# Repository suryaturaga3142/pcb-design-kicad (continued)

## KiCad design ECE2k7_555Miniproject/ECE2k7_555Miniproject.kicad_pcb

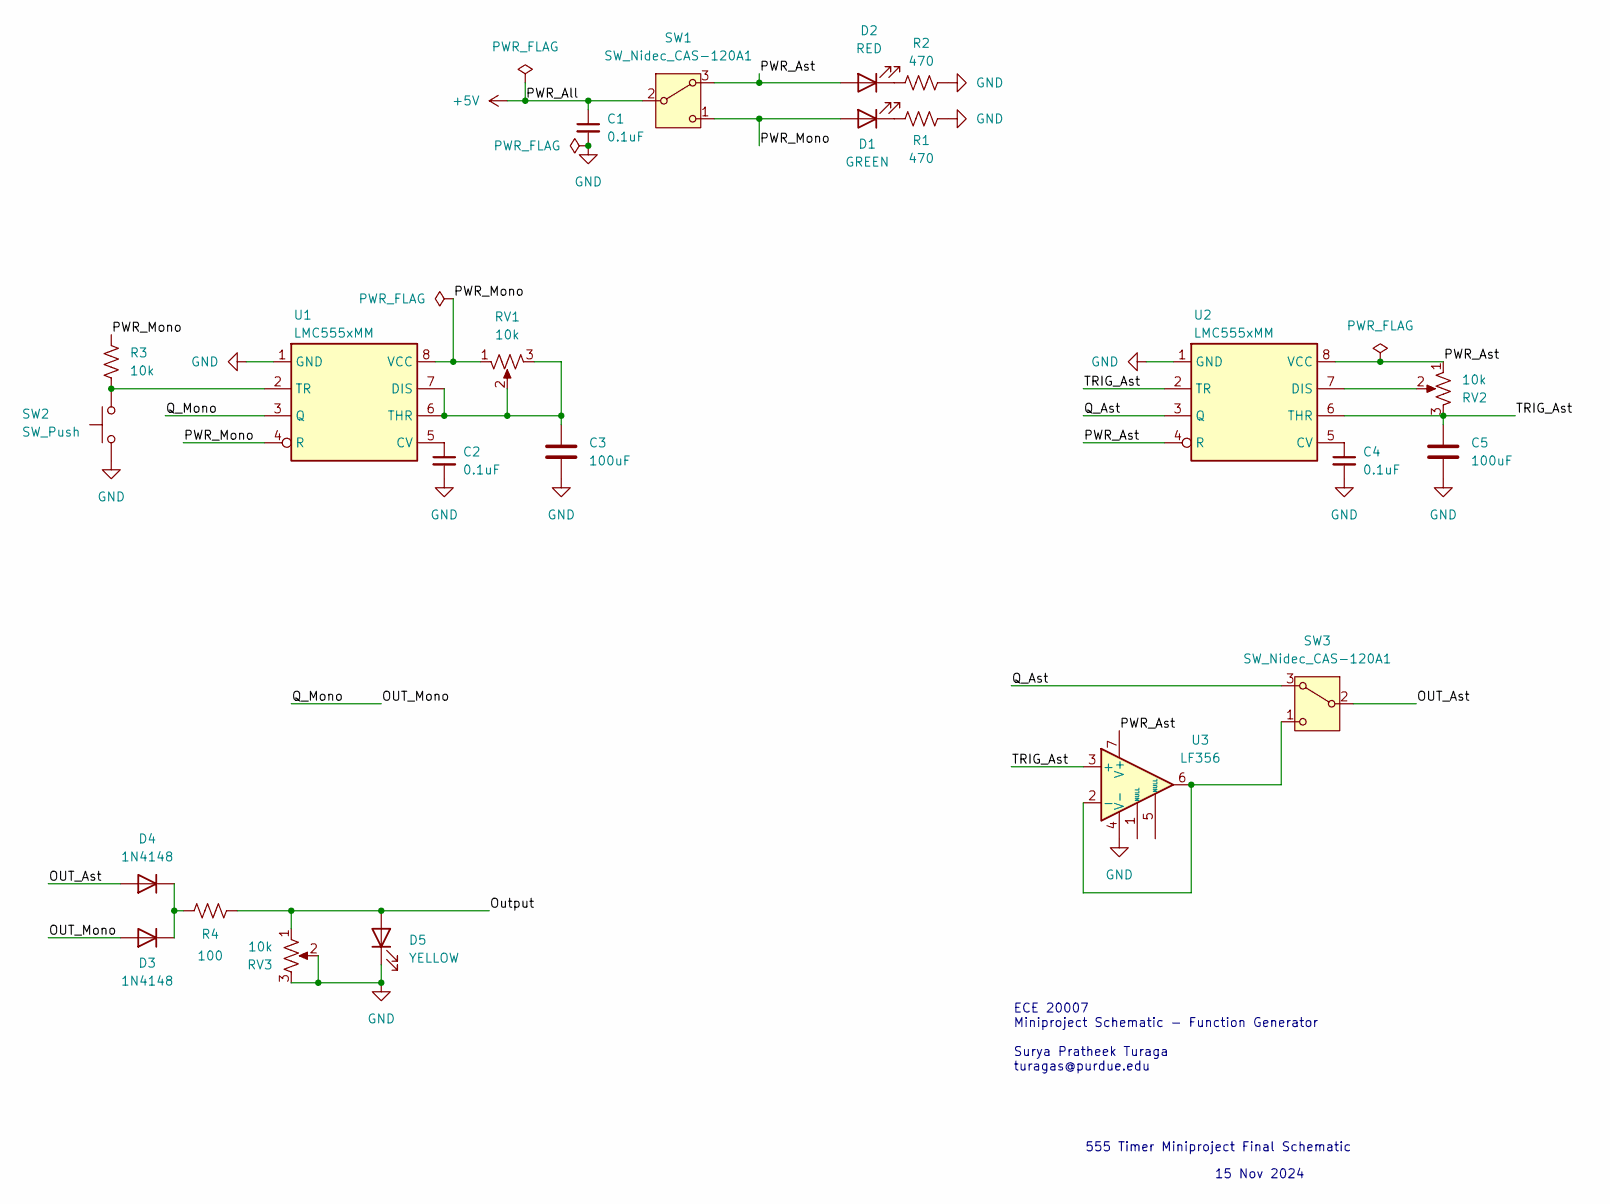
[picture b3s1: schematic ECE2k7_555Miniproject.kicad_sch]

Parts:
C1, C2, C4: 0.1uF; C_0201_0603Metric_Pad0.64x0.40mm_HandSolder
C3, C5: 100uF; C_0201_0603Metric_Pad0.64x0.40mm_HandSolder
D1: GREEN; LED_Rectangular_W5.0mm_H2.0mm
D2: RED; LED_Rectangular_W5.0mm_H2.0mm
D3, D4: 1N4148; D_DO-35_SOD27_P7.62mm_Horizontal
D5: YELLOW; LED_Rectangular_W5.0mm_H2.0mm
R1, R2: 470; R_Axial_DIN0204_L3.6mm_D1.6mm_P1.90mm_Vertical
R3: 10k; R_Axial_DIN0204_L3.6mm_D1.6mm_P1.90mm_Vertical
R4: 100; R_Axial_DIN0204_L3.6mm_D1.6mm_P1.90mm_Vertical
RV1, RV2, RV3: 10k; Potentiometer_ACP_CA9-H3,8_Horizontal
SW1, SW3: SW_Nidec_CAS-120A1; Nidec_Copal_CAS-120A
SW2: SW_Push; SW_PUSH_6mm_H5mm
U1, U2: LMC555xMM; VSSOP-8_3x3mm_P0.65mm
U3: LF356; DIP-8_W7.62mm_SMDSocket_SmallPads

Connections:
+5V: C1.1, SW1.2 (B)
/OUT_Ast: D4.2 (A), SW3.2 (B)
/OUT_Mono: D3.2 (A), U1.3 (Q)
/Output: D5.2 (A), R4.2, RV3.1
/PWR_Ast: D2.2 (A), RV2.1, SW1.3 (A), U2.4 (R), U2.8 (VCC), U3.7 (V+)
/PWR_Mono: D1.2 (A), R3.1, RV1.1, SW1.1 (C), U1.4 (R), U1.8 (VCC)
/Q_Ast: SW3.3 (A), U2.3 (Q)
/TRIG_Ast: C5.1, RV2.3, U2.2 (TR), U2.6 (THR), U3.3 (+)
GND: C1.2, C2.2, C3.2, C4.2, C5.2, D5.1 (K), R1.2, R2.2, RV3.2, RV3.3, SW2.1, U1.1 (GND), U2.1 (GND), U3.4 (V-)
unnamed: D1.1 (K), R1.1
unnamed: D2.1 (K), R2.1
unnamed: D3.1 (K), D4.1 (K), R4.1
unnamed: SW3.1 (C), U3.2 (-), U3.6
unnamed: C2.1, U1.5 (CV)
unnamed: C3.1, RV1.2, RV1.3, U1.6 (THR), U1.7 (DIS)
unnamed: R3.2, SW2.2, U1.2 (TR)
unnamed: C4.1, U2.5 (CV)
unnamed: RV2.2, U2.7 (DIS)

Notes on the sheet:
15 Nov 2024
555 Timer Miniproject Final Schematic
ECE 20007 Miniproject Schematic - Function Generator Surya Pratheek Turaga turagas@purdue.edu

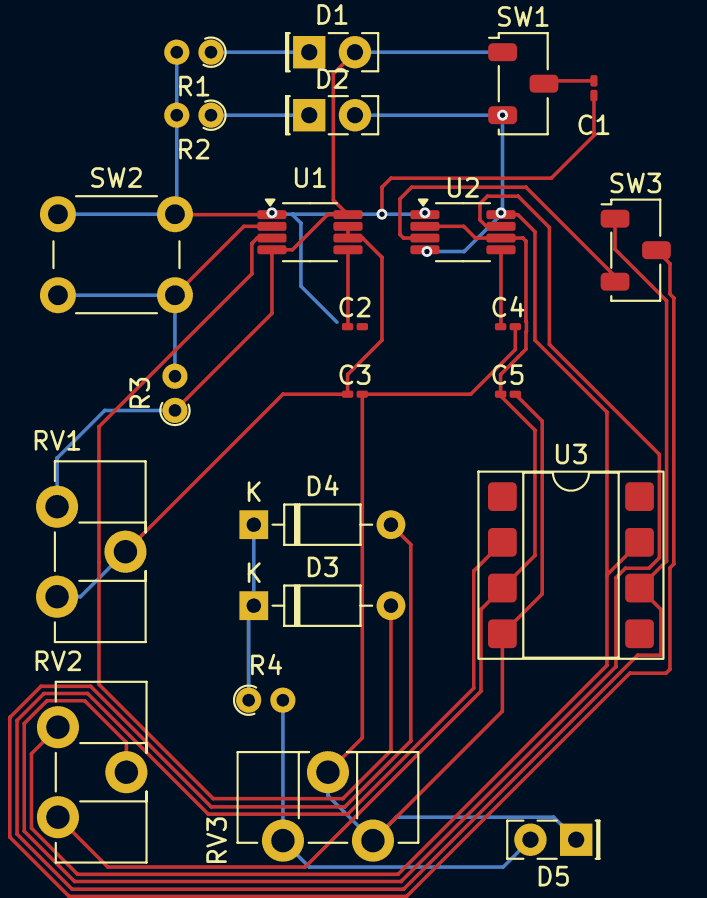
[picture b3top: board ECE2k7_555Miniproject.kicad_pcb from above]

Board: 2 copper layers, 23 parts (0 on the bottom side), 18 nets.

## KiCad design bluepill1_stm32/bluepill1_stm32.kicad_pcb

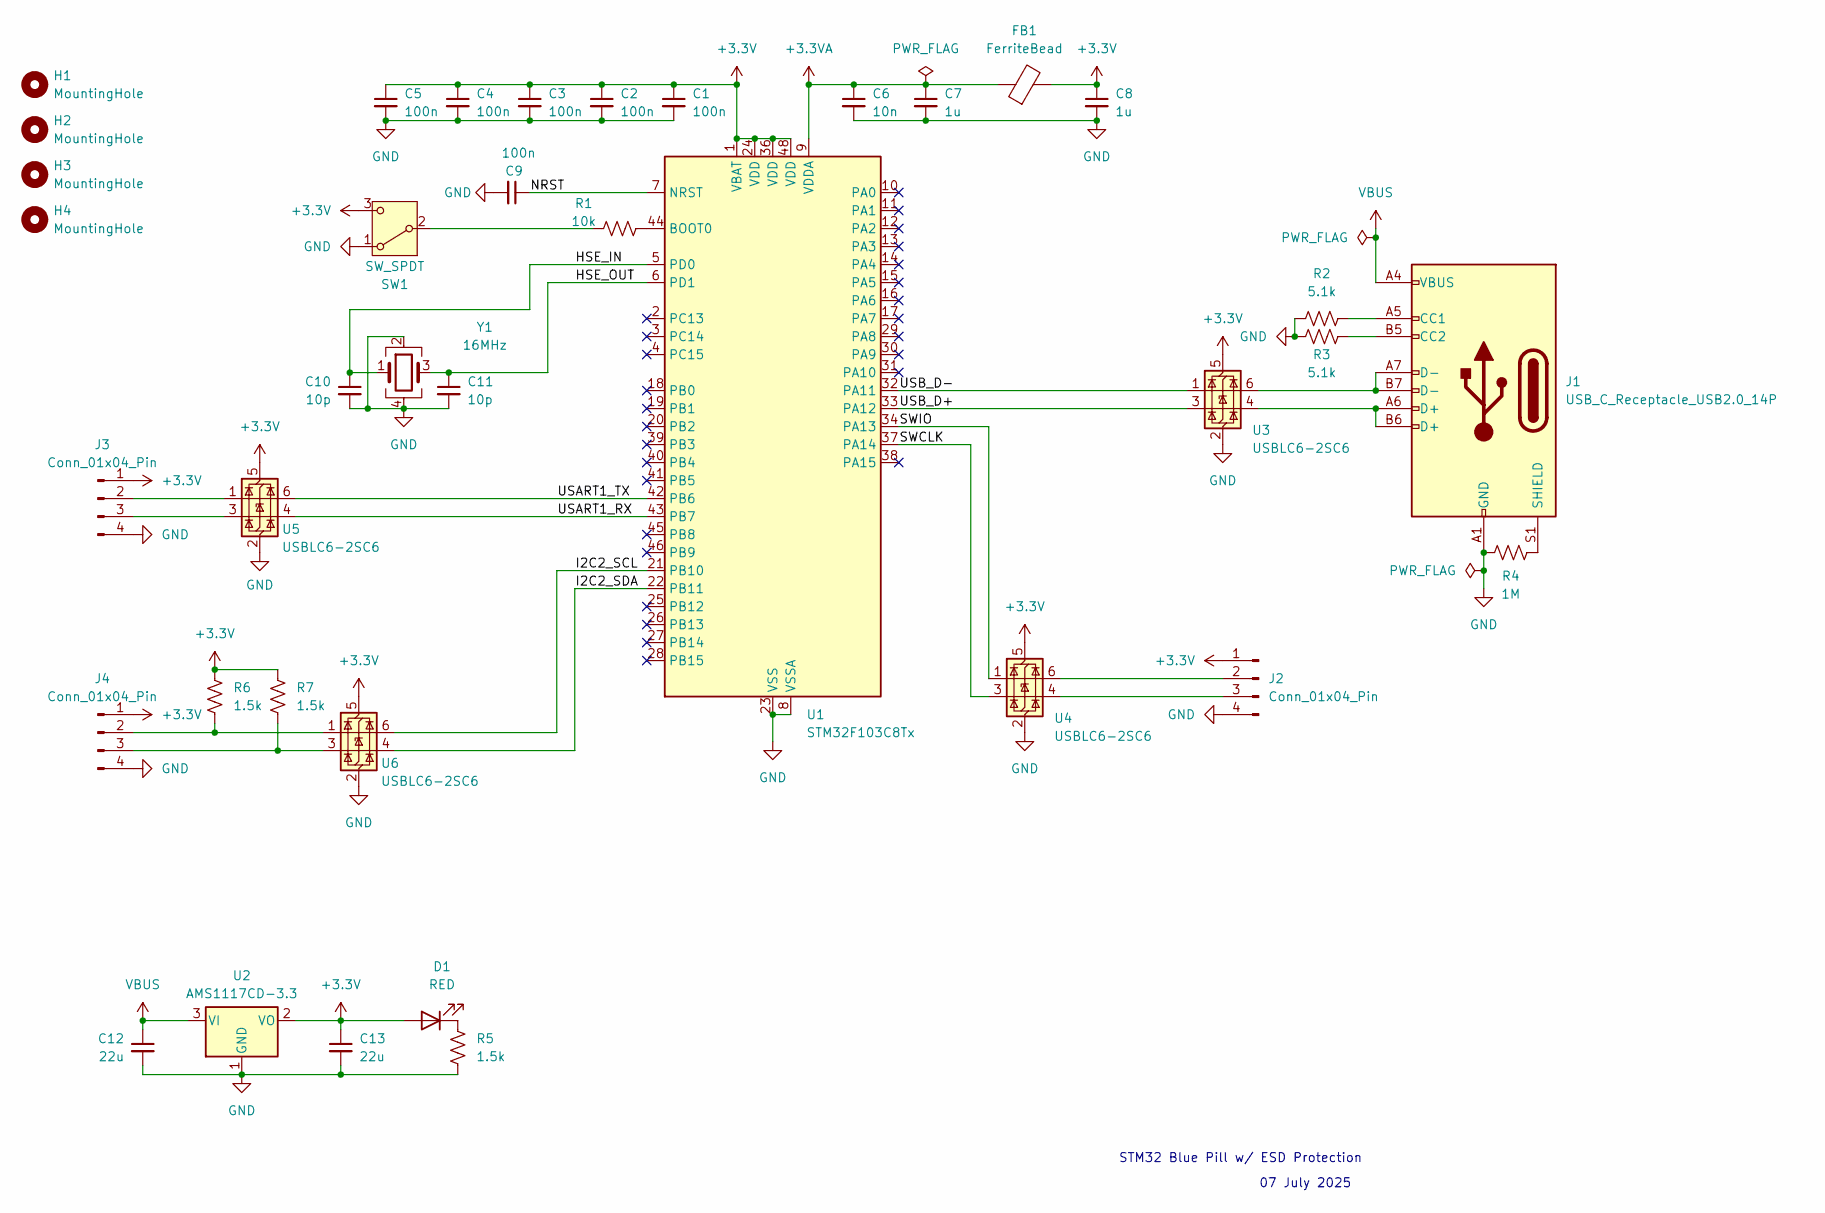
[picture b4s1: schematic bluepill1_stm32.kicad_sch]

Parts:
C1, C2, C3, C4, C5, C9: 100n; C_0402_1005Metric
C6: 10n; C_0402_1005Metric
C7, C8: 1u; C_0603_1608Metric
C10, C11: 10p; C_0402_1005Metric
C12, C13: 22u; C_0805_2012Metric
D1: RED; LED_0805_2012Metric
FB1: FerriteBead; L_0603_1608Metric
H1, H2, H3, H4: MountingHole; MountingHole_2.2mm_M2_DIN965
J1: USB_C_Receptacle_USB2.0_14P; USB_C_Receptacle_Amphenol_12401610E4-2A
J2, J3, J4: Conn_01x04_Pin; PinHeader_1x04_P2.54mm_Vertical
R1: 10k; R_0603_1608Metric
R2, R3: 5.1k; R_0603_1608Metric
R4: 1M; R_0603_1608Metric
R5, R6, R7: 1.5k; R_0603_1608Metric
SW1: SW_SPDT; SW_SPDT_PCM12
U1: STM32F103C8Tx; LQFP-48_7x7mm_P0.5mm
U2: AMS1117CD-3.3; TO-252-3_TabPin2
U3, U4, U5, U6: USBLC6-2SC6; SOT-23-6
Y1: 16MHz; Crystal_SMD_TXC_7M-4Pin_3.2x2.5mm_HandSoldering

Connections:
+3.3V: C1.1, C2.1, C3.1, C4.1, C5.1, C8.1, C13.1, D1.2 (A), FB1.2, J2.1, J3.1, J4.1, R6.1, R7.1, SW1.3 (C), U1.1 (VBAT), U1.24 (VDD), U1.36 (VDD), U1.48 (VDD), U2.2 (VO), U3.5 (VBUS), U4.5 (VBUS), U5.5 (VBUS), U6.5 (VBUS)
+3.3VA: C6.1, C7.1, FB1.1, U1.9 (VDDA)
/HSE_IN: C10.1, U1.5 (PD0), Y1.1
/HSE_OUT: C11.1, U1.6 (PD1), Y1.3
/I2C2_SCL: U1.21 (PB10), U6.6 (I/O1)
/I2C2_SDA: U1.22 (PB11), U6.4 (I/O2)
/NRST: C9.1, U1.7 (NRST)
/SWCLK: U1.37 (PA14), U4.3 (I/O2)
/SWIO: U1.34 (PA13), U4.1 (I/O1)
/USART1_RX: U1.43 (PB7), U5.4 (I/O2)
/USART1_TX: U1.42 (PB6), U5.6 (I/O1)
/USB_D+: U1.33 (PA12), U3.3 (I/O2)
/USB_D-: U1.32 (PA11), U3.1 (I/O1)
GND: C1.2, C2.2, C3.2, C4.2, C5.2, C6.2, C7.2, C8.2, C9.2, C10.2, C11.2, C12.2, C13.2, J1.A1 (GND), J1.A12 (GND), J1.B1 (GND), J1.B12 (GND), J2.4, J3.4, J4.4, R2.1, R3.1, R4.1, R5.2, SW1.1 (A), U1.8 (VSSA), U1.23 (VSS), U1.35 (VSS), U1.47 (VSS), U2.1 (GND), U3.2 (GND), U4.2 (GND), U5.2 (GND), U6.2 (GND), Y1.2, Y1.4
unnamed: D1.1 (K), R5.1
unnamed: J1.A5 (CC1), R2.2
unnamed: J1.B5 (CC2), R3.2
unnamed: J1.A6 (D+), J1.B6 (D+), U3.4 (I/O2)
unnamed: J1.A7 (D-), J1.B7 (D-), U3.6 (I/O1)
unnamed: J1.S1 (SHIELD), R4.2
unnamed: J2.2, U4.6 (I/O1)
unnamed: J2.3, U4.4 (I/O2)
unnamed: J3.2, U5.1 (I/O1)
unnamed: J3.3, U5.3 (I/O2)
unnamed: J4.2, R6.2, U6.1 (I/O1)
unnamed: J4.3, R7.2, U6.3 (I/O2)
unnamed: R1.1, SW1.2 (B)
unnamed: R1.2, U1.44 (BOOT0)
VBUS: C12.1, J1.A4 (VBUS), J1.A9 (VBUS), J1.B4 (VBUS), J1.B9 (VBUS), U2.3 (VI)

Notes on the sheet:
07 July 2025
STM32 Blue Pill w/ ESD Protection

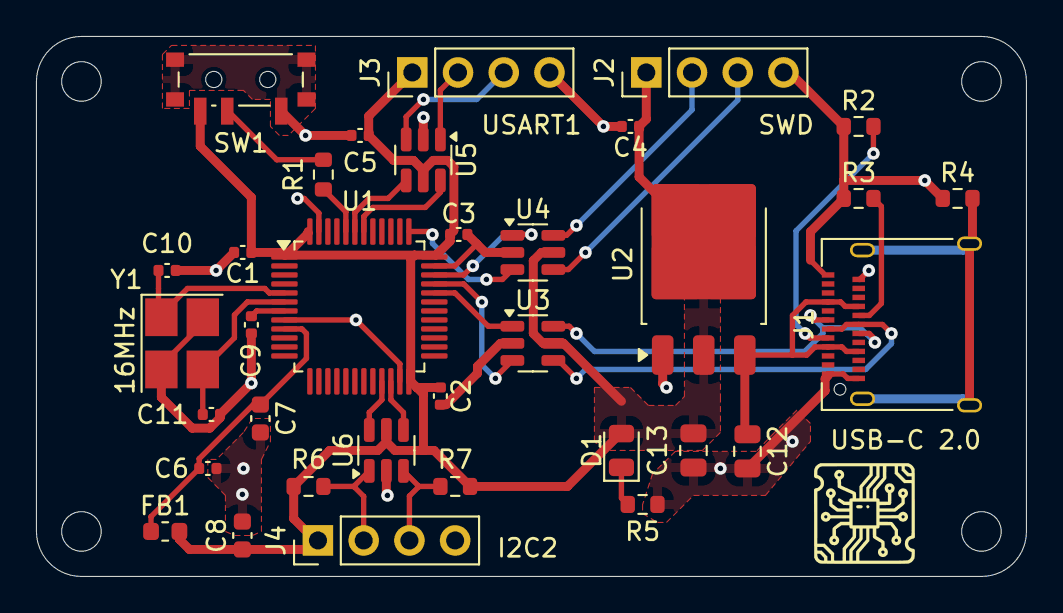
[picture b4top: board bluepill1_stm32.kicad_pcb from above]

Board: 2 copper layers, 55.0 x 30.0 mm, 38 parts (0 on the bottom side), 29 nets.

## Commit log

2025-07-09 Initial local commit
2025-07-09 Removed usb-demux
2025-07-09 readded usb
2025-07-15 Schematic done v1
2025-07-15 Circuit done
2025-07-16 Finished schematic
2025-07-19 PCB dsp v1 done
2025-09-07 flash adc setup
